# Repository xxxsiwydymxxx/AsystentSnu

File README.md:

Author: Piotr Szlejter
Project name: Asystent snu, urządzenie mierzące czynniki wpływające na sen
Description:
Urządzenie składa się z 2 części komunikujących się ze sobą bezprzewodowo
urządzenie bazowe posiada czujniki temperatury, ciśnienia atmosferycznego, 
wilgotności powietrza, dodatkowo zawiera czujnik ruchu i mikrofon, dodatkowo
 urządzenie posiada wyświetlacz / możliwość połączenia się z telefonem, 
 dodatkowo urządzenie może posiadać głośnik.
	Urządzenie dodatkowe jest zakładane na nadgarstek/palec i posiada 
pulsometr, oraz czujnik nasycenia krwi tlenem.
	Działanie: urządzenie wykonuje pomiary podczas snu i wyświetla je 
na wyświetlaczu oraz zapisuje do pamięci, dodatkowo urządzenie może 
odtwarzać biały szum przez wbudowany głośnik

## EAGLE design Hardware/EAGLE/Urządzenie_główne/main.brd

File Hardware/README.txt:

Schematy zostały wykonane w programie KiCAD

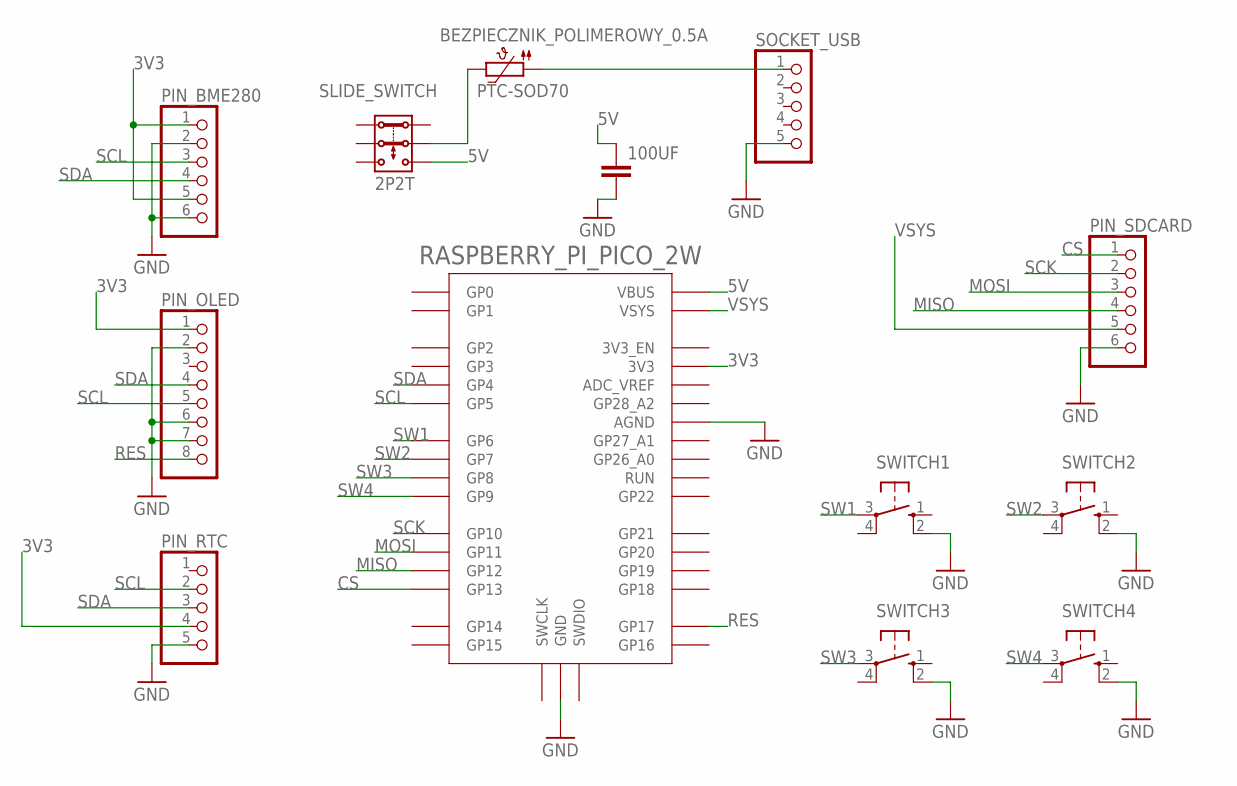
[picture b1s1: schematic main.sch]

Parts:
100UF: C2,5-3; C2.5-3
BEZPIECZNIK_POLIMEROWY_0.5A: PTC-SOD70; SOD70
PIN_BME280: PINHD-1X6; 1X06
PIN_OLED: PINHD-1X8; 1X08
PIN_RTC: PINHD-1X5; 1X05
PIN_SDCARD: PINHD-1X6; 1X06
RASPBERRY_PI_PICO_2W: RPI_PICO-TH; RPI_PICO_TH
SLIDE_SWITCH: 2P2T
SOCKET_USB: PINHD-1X5; 1X05
SWITCH1, SWITCH2, SWITCH3, SWITCH4: 10-XX; B3F-10XX

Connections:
3V3: PIN_BME280.1, PIN_BME280.5, PIN_OLED.1, PIN_RTC.4, RASPBERRY_PI_PICO_2W.3V3
5V: 100UF.1, RASPBERRY_PI_PICO_2W.VBUS, SLIDE_SWITCH.3.1
CS: PIN_SDCARD.1, RASPBERRY_PI_PICO_2W.GP13
GND: 100UF.2, PIN_BME280.2, PIN_BME280.6, PIN_OLED.2, PIN_OLED.6, PIN_OLED.7, PIN_RTC.5, PIN_SDCARD.6, RASPBERRY_PI_PICO_2W.AGND, RASPBERRY_PI_PICO_2W.GND@1 (GND), RASPBERRY_PI_PICO_2W.GND@2 (GND), RASPBERRY_PI_PICO_2W.GND@3 (GND), RASPBERRY_PI_PICO_2W.GND@4 (GND), RASPBERRY_PI_PICO_2W.GND@5 (GND), RASPBERRY_PI_PICO_2W.GND@6 (GND), RASPBERRY_PI_PICO_2W.GND@7 (GND), RASPBERRY_PI_PICO_2W.GND@8 (GND), SOCKET_USB.5, SWITCH1.2 (S1), SWITCH2.2 (S1), SWITCH3.2 (S1), SWITCH4.2 (S1)
MISO: PIN_SDCARD.4, RASPBERRY_PI_PICO_2W.GP12
MOSI: PIN_SDCARD.3, RASPBERRY_PI_PICO_2W.GP11
unnamed: BEZPIECZNIK_POLIMEROWY_0.5A.1, SOCKET_USB.1
unnamed: BEZPIECZNIK_POLIMEROWY_0.5A.2, SLIDE_SWITCH.2.1
RES: PIN_OLED.8, RASPBERRY_PI_PICO_2W.GP17
SCK: PIN_SDCARD.2, RASPBERRY_PI_PICO_2W.GP10
SCL: PIN_BME280.3, PIN_OLED.5, PIN_RTC.2, RASPBERRY_PI_PICO_2W.GP5
SDA: PIN_BME280.4, PIN_OLED.4, PIN_RTC.3, RASPBERRY_PI_PICO_2W.GP4
SW1: RASPBERRY_PI_PICO_2W.GP6, SWITCH1.3
SW2: RASPBERRY_PI_PICO_2W.GP7, SWITCH2.3
SW3: RASPBERRY_PI_PICO_2W.GP8, SWITCH3.3
SW4: RASPBERRY_PI_PICO_2W.GP9, SWITCH4.3
VSYS: PIN_SDCARD.5, RASPBERRY_PI_PICO_2W.VSYS

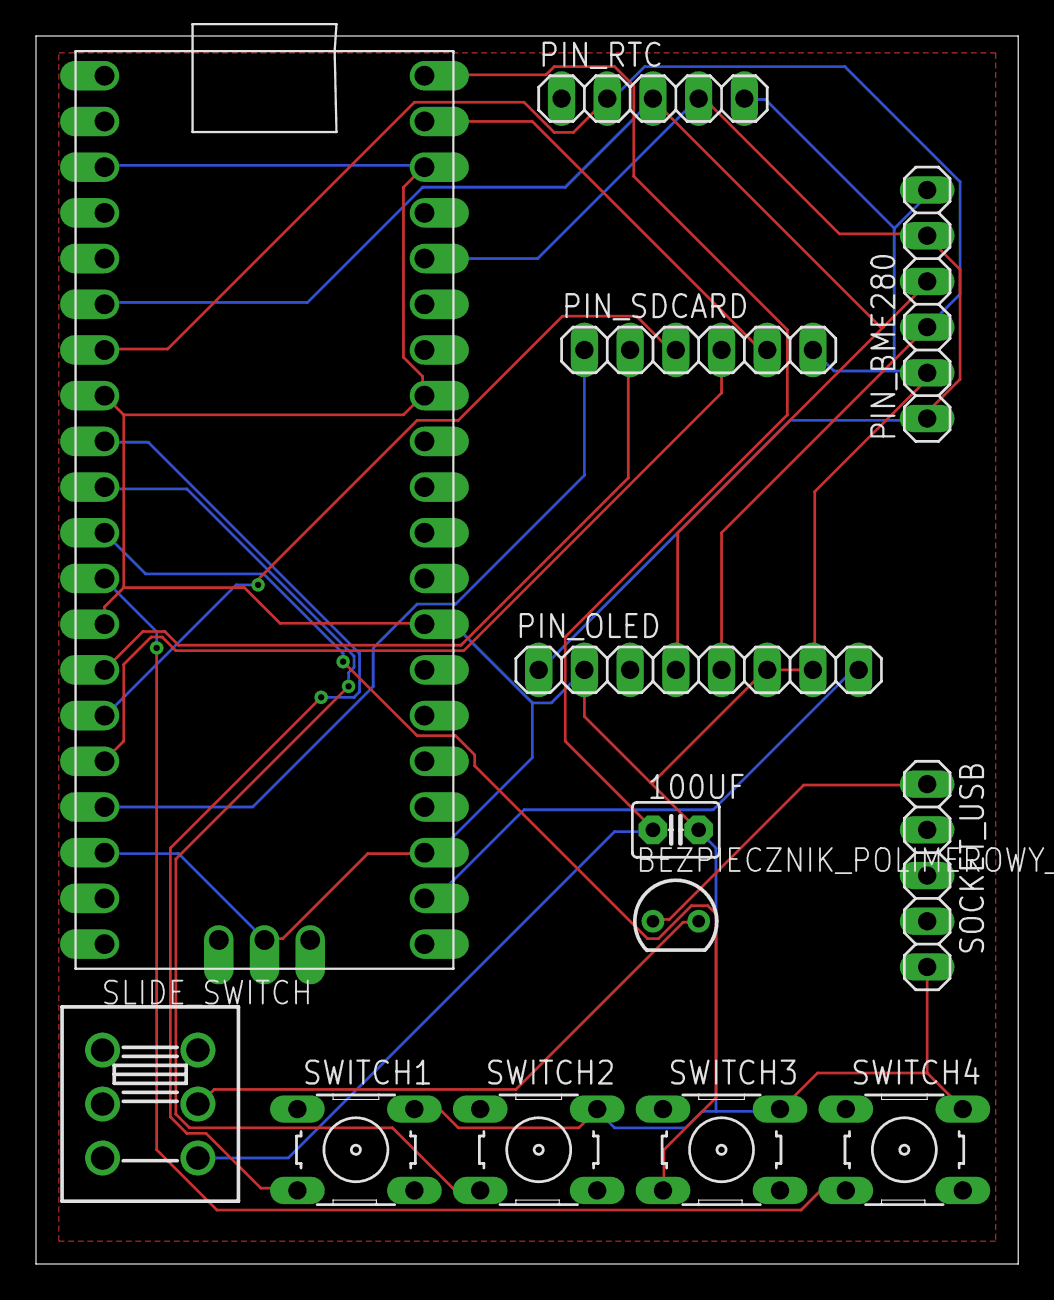
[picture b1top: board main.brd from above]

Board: 2 copper layers, 54.6 x 68.2 mm, 13 parts (0 on the bottom side), 17 nets.

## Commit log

2026-02-16 removed comments
2026-02-19 fixed according to instructions
2026-02-19 added old board pdf
2026-02-20 prezentacja w formacie pdf
